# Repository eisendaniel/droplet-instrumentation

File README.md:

# Repository Directory Structure

### Documents

Any files which aren't _Literature_, i.e. anything that won't or can't be cited.

### Literature

A flat folder containing PDF copies of anything that will or could be cited in the reports: journal articles, tech notes, etc.  There should be a BibTeX `.bib` bibliography file at the same level as the PDF files, for use with the [JabRef](http://www.jabref.org) open source bibliography and reference manager.

### Presentations

The files used in any presentations, including the final presentation.

VBUS
* R, Matlab, etc. files, containing _only_ the figures used in the report at this level.
* One sub-folder "Figures" to keep figures organised.

Home: O
Res: 55
Targ: 172

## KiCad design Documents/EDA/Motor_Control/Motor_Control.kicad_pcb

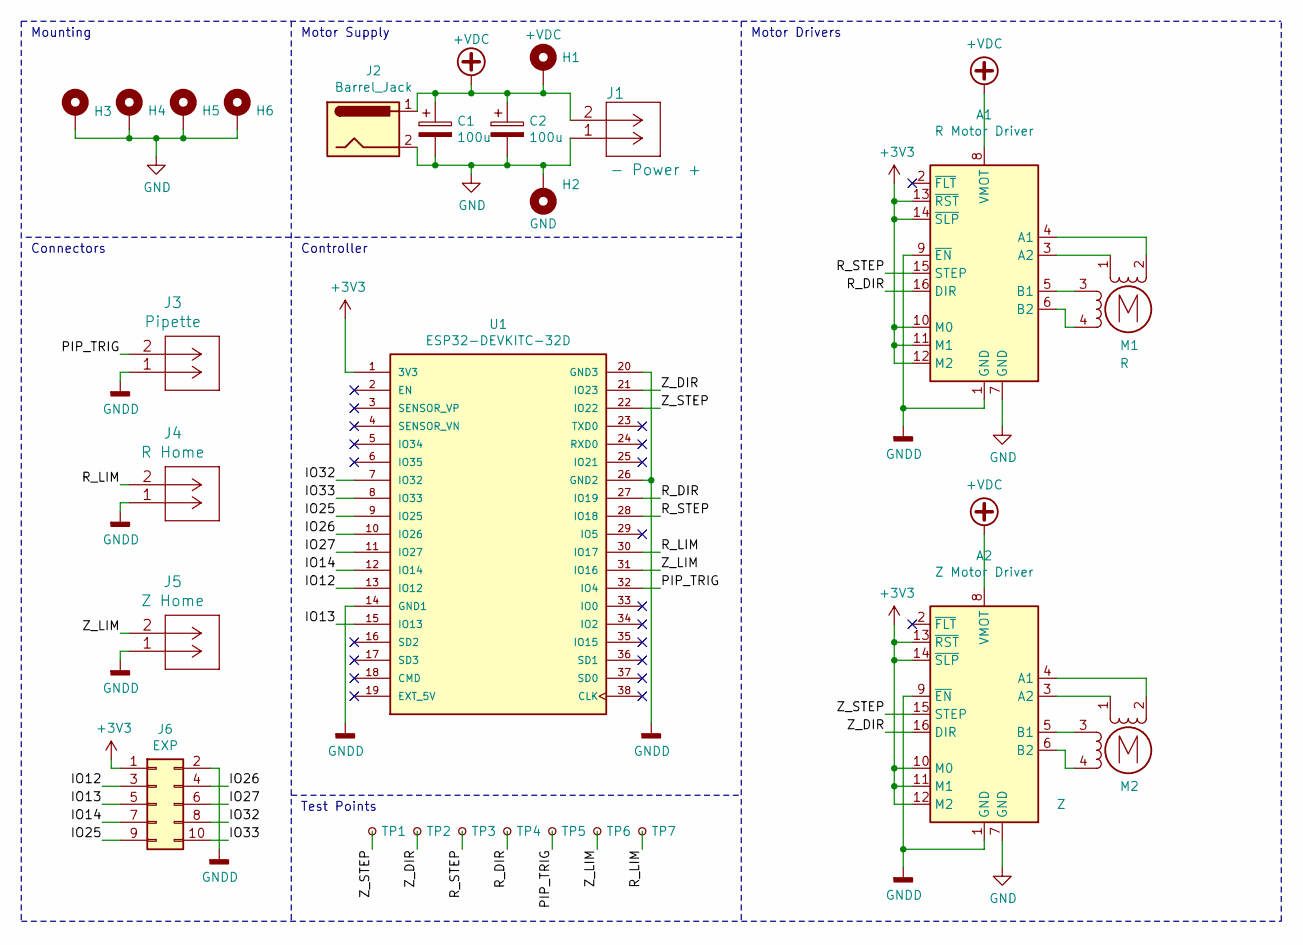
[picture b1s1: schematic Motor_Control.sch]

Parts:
A1: R Motor Driver; Pololu_Breakout-16_15.2x20.3mm
A2: Z Motor Driver; Pololu_Breakout-16_15.2x20.3mm
C1, C2: 100u; CP_Radial_D8.0mm_P3.50mm
H1: +VDC; MountingHole_3.7mm_Pad_Via
H2: GND; MountingHole_3.7mm_Pad_Via
H3, H4, H5, H6: øM3; MountingHole_3.2mm_M3_Pad_Via
J1: - Power +; molex_sherlock_vrthdr_2pin
J2: Barrel_Jack; BarrelJack_Horizontal; man part # PJ-002BH
J3: Pipette; molex_sherlock_vrthdr_2pin
J4: R Home; molex_sherlock_vrthdr_2pin
J5: Z Home; molex_sherlock_vrthdr_2pin
J6: EXP; PinHeader_2x05_P2.54mm_Vertical
M1: R; molex_sherlock_vrthdr_4pin
M2: Z; molex_sherlock_vrthdr_4pin
TP1: Z_STEP; TestPoint_Pad_D1.0mm
TP2: Z_DIR; TestPoint_Pad_D1.0mm
TP3: R_STEP; TestPoint_Pad_D1.0mm
TP4: R_DIR; TestPoint_Pad_D1.0mm
TP5: PIP_TRIG; TestPoint_Pad_D1.0mm
TP6: Z_LIM; TestPoint_Pad_D1.0mm
TP7: R_LIM; TestPoint_Pad_D1.0mm
U1: ESP32-DEVKITC-32D; MODULE_ESP32-DEVKITC-32D; PARTREV 4

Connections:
+3V3: A1.10 (M0), A1.11 (M1), A1.12 (M2), A1.13 (~RST), A1.14 (~SLP), A2.10 (M0), A2.11 (M1), A2.12 (M2), A2.13 (~RST), A2.14 (~SLP), J6.1, U1.1 (3V3)
+VDC: A1.8 (VMOT), A2.8 (VMOT), C1.1, C2.1, H1.1, J1.2, J2.1
/IO12: J6.3, U1.13 (IO12)
/IO13: J6.5, U1.15 (IO13)
/IO14: J6.7, U1.12 (IO14)
/IO25: J6.9, U1.9 (IO25)
/IO26: J6.4, U1.10 (IO26)
/IO27: J6.6, U1.11 (IO27)
/IO32: J6.8, U1.7 (IO32)
/IO33: J6.10, U1.8 (IO33)
/PIP_TRIG: J3.2, TP5.1, U1.32 (IO4)
/R_DIR: A1.16 (DIR), TP4.1, U1.27 (IO19)
/R_LIM: J4.2, TP7.1, U1.30 (IO17)
/R_STEP: A1.15 (STEP), TP3.1, U1.28 (IO18)
/Z_DIR: A2.16 (DIR), TP2.1, U1.21 (IO23)
/Z_LIM: J5.2, TP6.1, U1.31 (IO16)
/Z_STEP: A2.15 (STEP), TP1.1, U1.22 (IO22)
GND: A1.7 (GND), A2.7 (GND), C1.2, C2.2, H2.1, H3.1, H4.1, H5.1, H6.1, J1.1, J2.2
GNDD: A1.1 (GND), A1.9 (~EN), A2.1 (GND), A2.9 (~EN), J3.1, J4.1, J5.1, J6.2, U1.14 (GND1), U1.20 (GND3), U1.26 (GND2)
unnamed: A1.3 (A2), M1.1
unnamed: A1.4 (A1), M1.2 (-)
unnamed: A1.5 (B1), M1.3
unnamed: A1.6 (B2), M1.4
unnamed: A2.3 (A2), M2.1
unnamed: A2.4 (A1), M2.2 (-)
unnamed: A2.5 (B1), M2.3
unnamed: A2.6 (B2), M2.4

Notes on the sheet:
Motor Supply
Motor Drivers
Controller
Connectors
Mounting
Test Points

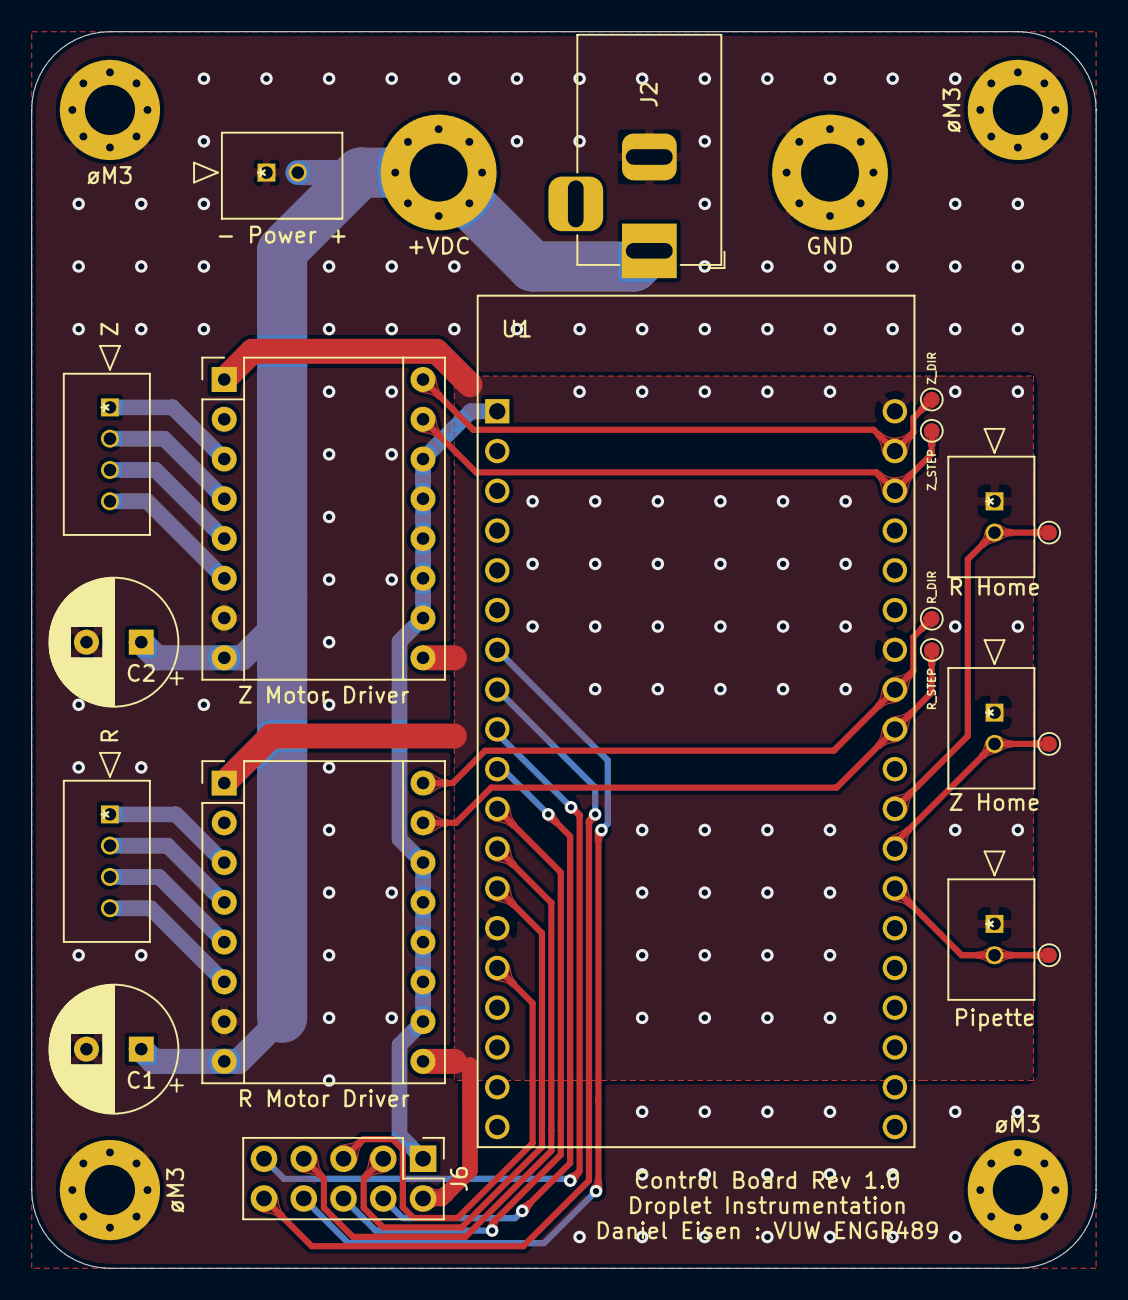
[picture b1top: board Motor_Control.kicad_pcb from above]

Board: 2 copper layers, 68.0 x 79.0 mm, 26 parts (0 on the bottom side), 27 nets.

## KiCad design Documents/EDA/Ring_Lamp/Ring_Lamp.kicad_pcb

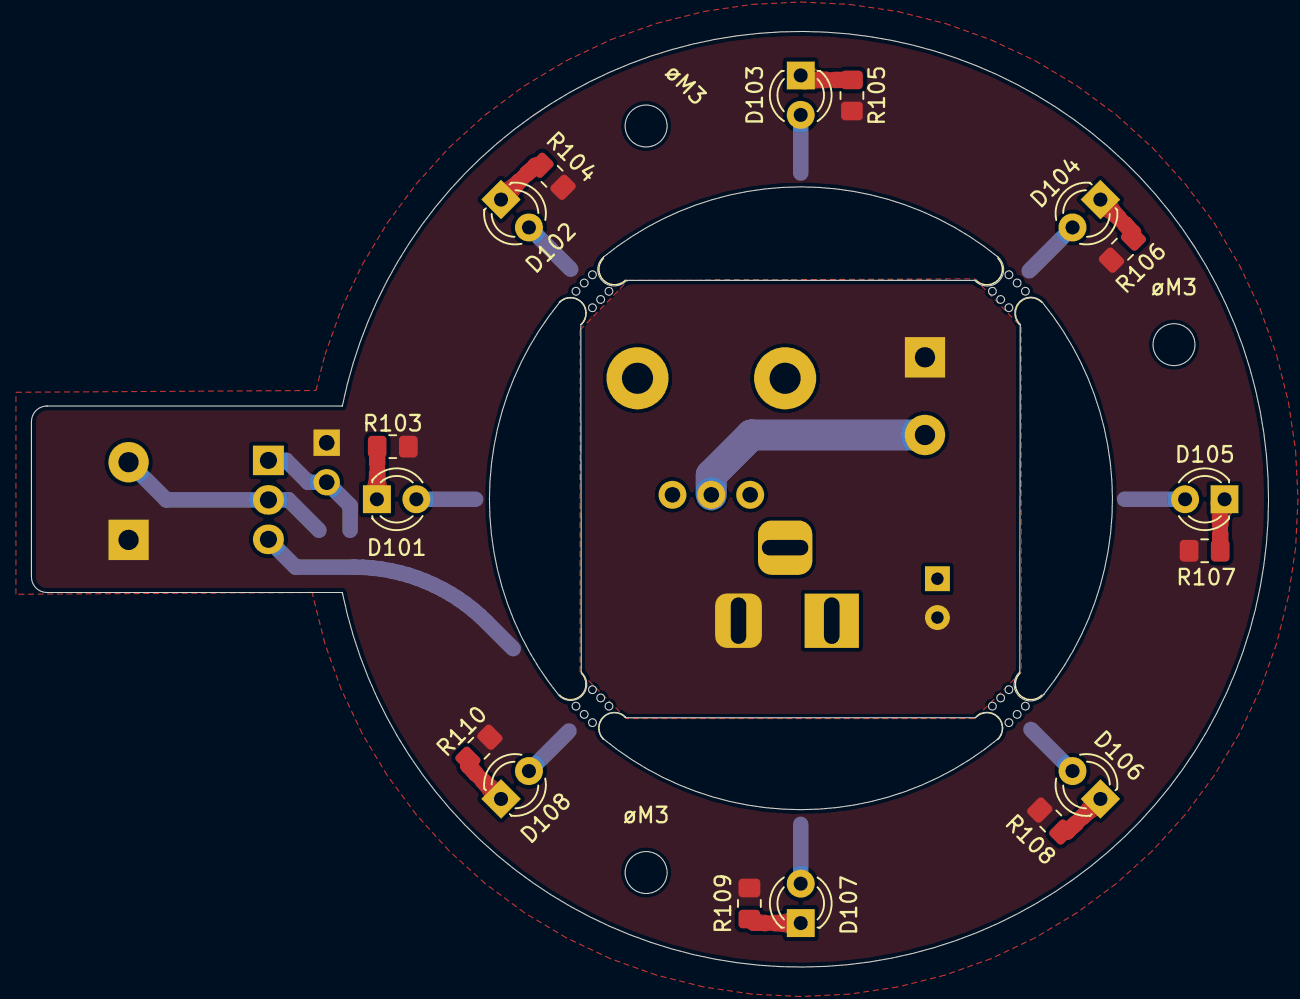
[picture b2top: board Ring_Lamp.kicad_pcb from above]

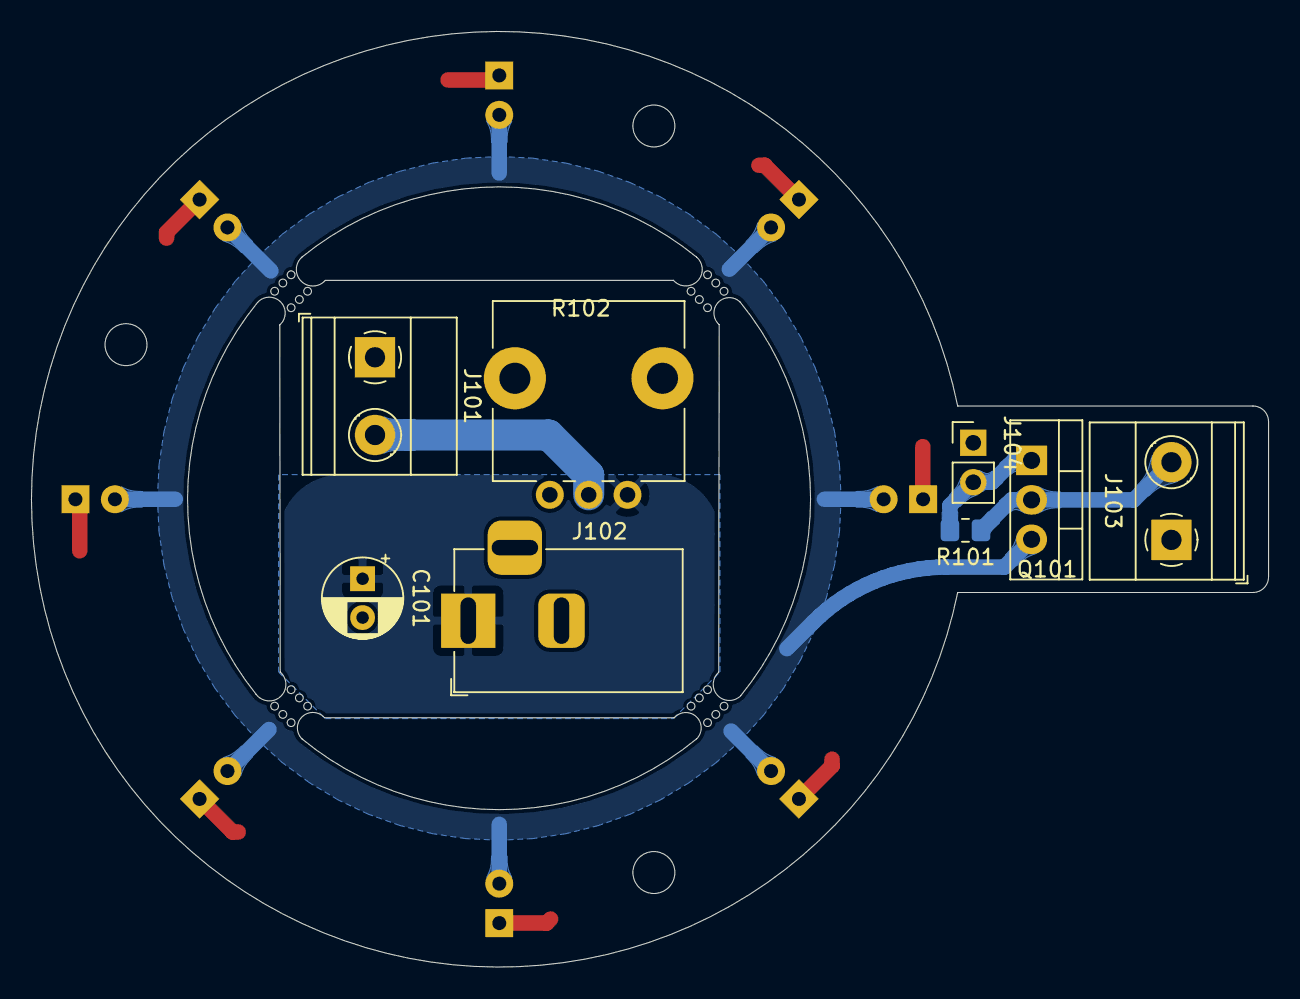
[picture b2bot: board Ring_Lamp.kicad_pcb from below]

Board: 2 copper layers, 79.6 x 60.2 mm, 31 parts (8 on the bottom side), 13 nets.

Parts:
C101: 100u; CP_Radial_D5.0mm_P2.50mm
D101, D102, D103, D104, D105, D106, D107, D108: LED; LED_D3.0mm_Clear
J101: CTRL_V_LED; TerminalBlock_Phoenix_MKDS-1,5-2_1x02_P5.00mm_Horizontal
J102: Barrel_Jack; BarrelJack_Horizontal
J103: RING_V_LED; TerminalBlock_Phoenix_MKDS-1,5-2_1x02_P5.00mm_Horizontal
J104: ENABLE; PinHeader_1x02_P2.54mm_Vertical
Q101: Q_NMOS_GDS; TO-220-3_Vertical
R101: 10k; R_0805_2012Metric_Pad1.20x1.40mm_HandSolder
R102: 10k; Potentiometer_Alps_RK09L_Single_Vertical
R103, R104, R105, R106, R107, R108, R109, R110: 100; R_0805_2012Metric_Pad1.20x1.40mm_HandSolder
mouse-bite-2mm-slot, mouse-bite-2mm-slot#2, mouse-bite-2mm-slot#3, mouse-bite-2mm-slot#4: VAL**; mouse-bite-2mm-slot
øM3, øM3#2, øM3#3: MountingHole; MountingHole_2.7mm_M2.5

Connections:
/ENABLE: J104.2, Q101.1, R101.2
/LED_BUS: D101.2, D102.2, D103.2, D104.2, D105.2, D106.2, D107.2, D108.2, Q101.3
/V_LED: J101.2, J103.2, Q101.2, R101.1, R102.2
GND: C101.2, J101.1, J102.2, J103.1, J104.1, R103.1, R104.1, R105.1, R106.1, R107.1, R108.1, R109.1, R110.1
unnamed: D101.1, R103.2
unnamed: D102.1, R104.2
unnamed: D103.1, R105.2
unnamed: D104.1, R106.2
unnamed: D105.1, R107.2
unnamed: D106.1, R108.2
unnamed: D107.1, R109.2
unnamed: D108.1, R110.2
VDD: C101.1, J102.1, R102.1

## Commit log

2021-03-10 Setup latex project and filled in details
2021-03-10 Added timelog, cleaned proj_prop
2021-03-11 markdown and prop
2021-03-14 prop_draft
2021-03-15 Proposal draft, problem and solution
2021-03-15 Drafted major sections
2021-03-15 rm tempkate filler
2021-03-16 notes
2021-03-17 prop and notes
2021-03-18 TODO, intro and covid
2021-03-18 cleaned aux
2021-03-19 ammeded grammer, oops
2021-03-30 motor research
2021-03-30 links
2021-05-05 Updated mount and stage spec
2021-05-18 BOM coml, datasheets added, prelim started
2021-05-19 prelim andatasheets
2021-05-19 parts and cad
2021-05-24 prelim
2021-05-25 laptop->desktop sync
2021-06-04 motor addition to cad/eda and datasheets
2021-06-08 Base control software
2021-06-09 clean frag
2021-06-15 begin serial input parsing
2021-06-15 FIN v0.1 of serial control
2021-06-15 hotfix: Serial printing
2021-06-17 z micrometer coupler stl
2021-06-18 serial debug
2021-06-28 z mount fin rev 1
2021-07-18 sequence and delays
2021-07-19 Labview controller: seq in prog
2021-07-19 PCB first pass
2021-07-21 match lost code
2021-08-03 datasheet
2021-08-03 PIP trippering comple
2021-08-11 Tuned params and fixed char limit
2021-08-16 rev 2 parts
2021-08-17 libs and pcb and bom
2021-08-17 connectors placed
2021-08-26 Final pcb and bom
2021-09-16 PCB complete and ordered
2021-09-16 final report
2021-09-16 Final report fig
2021-09-16 environmental monitor
2021-09-16 Refactor to cleanup main
2021-09-19 draft 0.5
2021-09-19 filling out the bones
2021-09-21 data
2021-09-21 labview control
2021-09-21 rm Z motion vib via speed decrease
2021-09-21 full requirents
2021-09-22 temp aq
2021-09-26 calibration images 22_9
2021-09-28 reimplented deep sleep to fix pin alarm and sleep periferals
2021-09-28 Enable timer reset
2021-09-28 env moniter complt
2021-10-01 report draft 2 inm prog
2021-10-04 d2 ip
2021-10-05 prog
2021-10-06 env mon fig
2021-10-06 design z
2021-10-06 env andnz
2021-10-07 feedback impl, abs done, design todo
2021-10-09 impl + eval
2021-10-09 almost fin
2021-10-13 pres
2021-10-18 rot R in deg
2021-11-04 Ring light for camera illum
2021-11-14 ring light
2021-11-14 py gui
2021-11-16 switched to QtSerial and cleaned layout
2021-11-17 GUI cmpl and homing added
2021-11-22 homing fully intergrated
2021-11-22 refact
2021-11-25 special position
2021-11-26 grid layout cleaneed
2021-11-26 standalone bin
2021-11-29 tested cleanup
2021-11-30 nice and pretty
2021-12-01 auto Z motion for safety and controller tracks pos
2021-12-03 standard seq
2021-12-03 color coding
2021-12-05 present sequence selection
2021-12-07 headers
2021-12-13 GUI camera config and control
2021-12-13 rm typing for compat
2021-12-13 layout cleaned
2021-12-15 camera triggering
2021-12-15 names
2022-01-12 daq_test py and graphing
2022-01-12 time vec
2022-01-17 daqmx wkin
2022-01-19 TDMS Logging fully functional
2022-01-30 graph update signal
2022-02-02 fine z control and milk seq
2022-02-02 sync
2022-02-02 duel serial
2022-02-03 atmos read into TDMS

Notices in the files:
parts and their libraries:
Copyright 2021 Accelerated Designs. All rights reserved.
